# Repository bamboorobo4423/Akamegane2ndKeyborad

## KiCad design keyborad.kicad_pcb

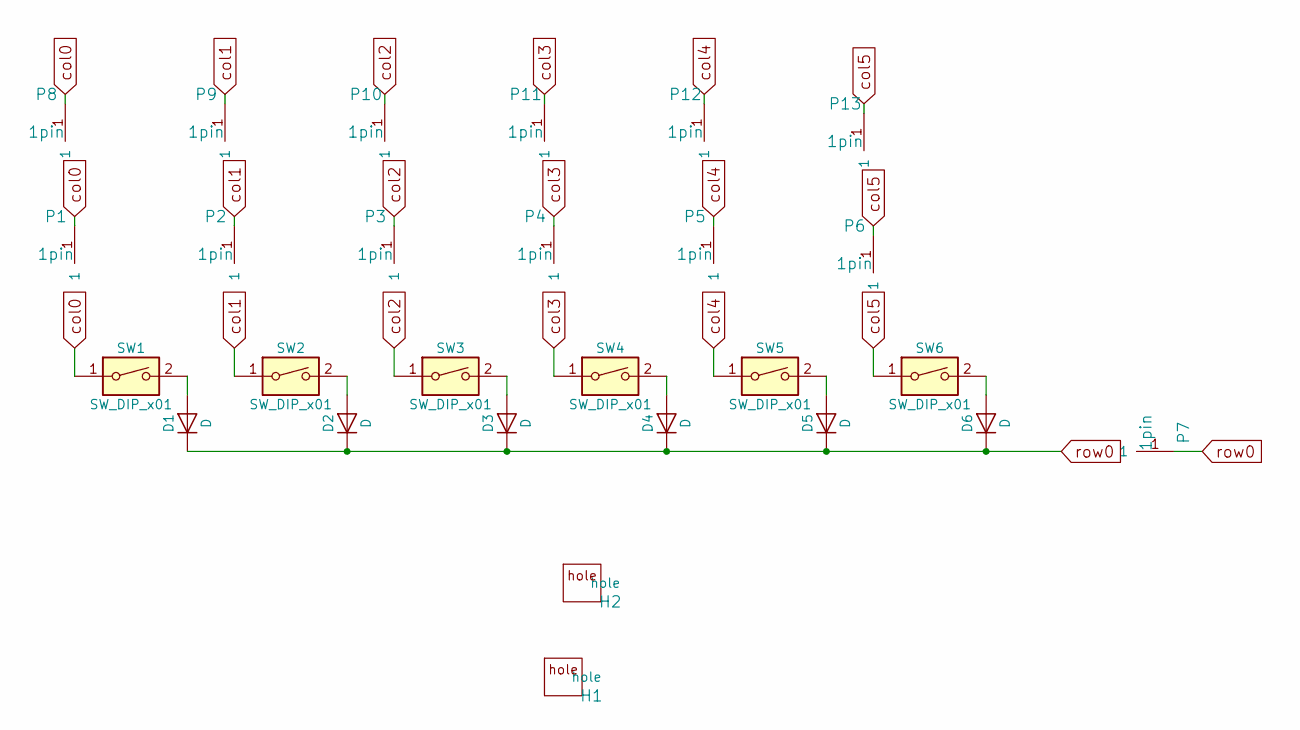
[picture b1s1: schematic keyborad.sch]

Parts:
D1, D2, D3, D4, D5, D6: D; Diode
H1, H2: hole; MountingHole_3.2mm_M3_Pad
P1, P2, P3, P4, P5, P6, P7, P8, P9, P10, P11, P12, P13: 1pin; Pin_Header_Straight_1x01_Pitch1.27mm
SW1, SW2, SW3, SW4, SW5, SW6: SW_DIP_x01; Kailh-PG1350-1u-reversible

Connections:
unnamed: D1.2 (A), SW1.2
unnamed: D2.2 (A), SW2.2
unnamed: D3.2 (A), SW3.2
unnamed: D4.2 (A), SW4.2
unnamed: D5.2 (A), SW5.2
unnamed: D6.2 (A), SW6.2
col0: P1.1, P8.1, SW1.1
col1: P2.1, P9.1, SW2.1
col2: P3.1, P10.1, SW3.1
col3: P4.1, P11.1, SW4.1
col4: P5.1, P12.1, SW5.1
col5: P6.1, P13.1, SW6.1
row0: D1.1 (K), D2.1 (K), D3.1 (K), D4.1 (K), D5.1 (K), D6.1 (K), P7.1

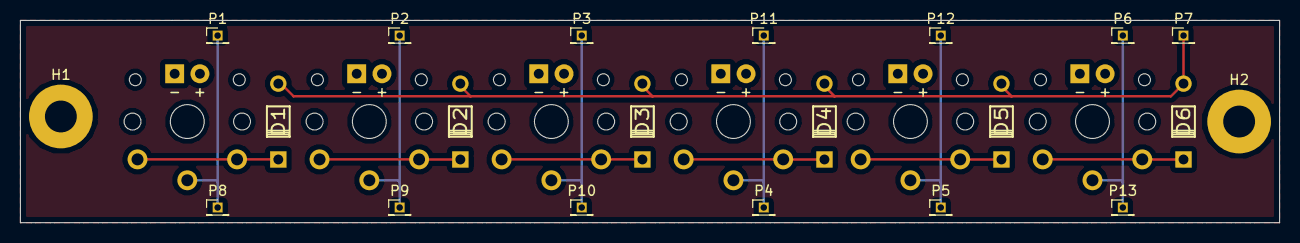
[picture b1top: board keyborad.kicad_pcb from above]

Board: 2 copper layers, 126.5 x 20.3 mm, 27 parts (0 on the bottom side), 13 nets.

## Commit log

2018-06-01 ネットリストの更新
2018-06-01 ちまちま修正
    いらないファイルたちは消した
2018-06-03 とりあえず形にした
2018-08-10 とりあえず使えそうだからガーバーだした
